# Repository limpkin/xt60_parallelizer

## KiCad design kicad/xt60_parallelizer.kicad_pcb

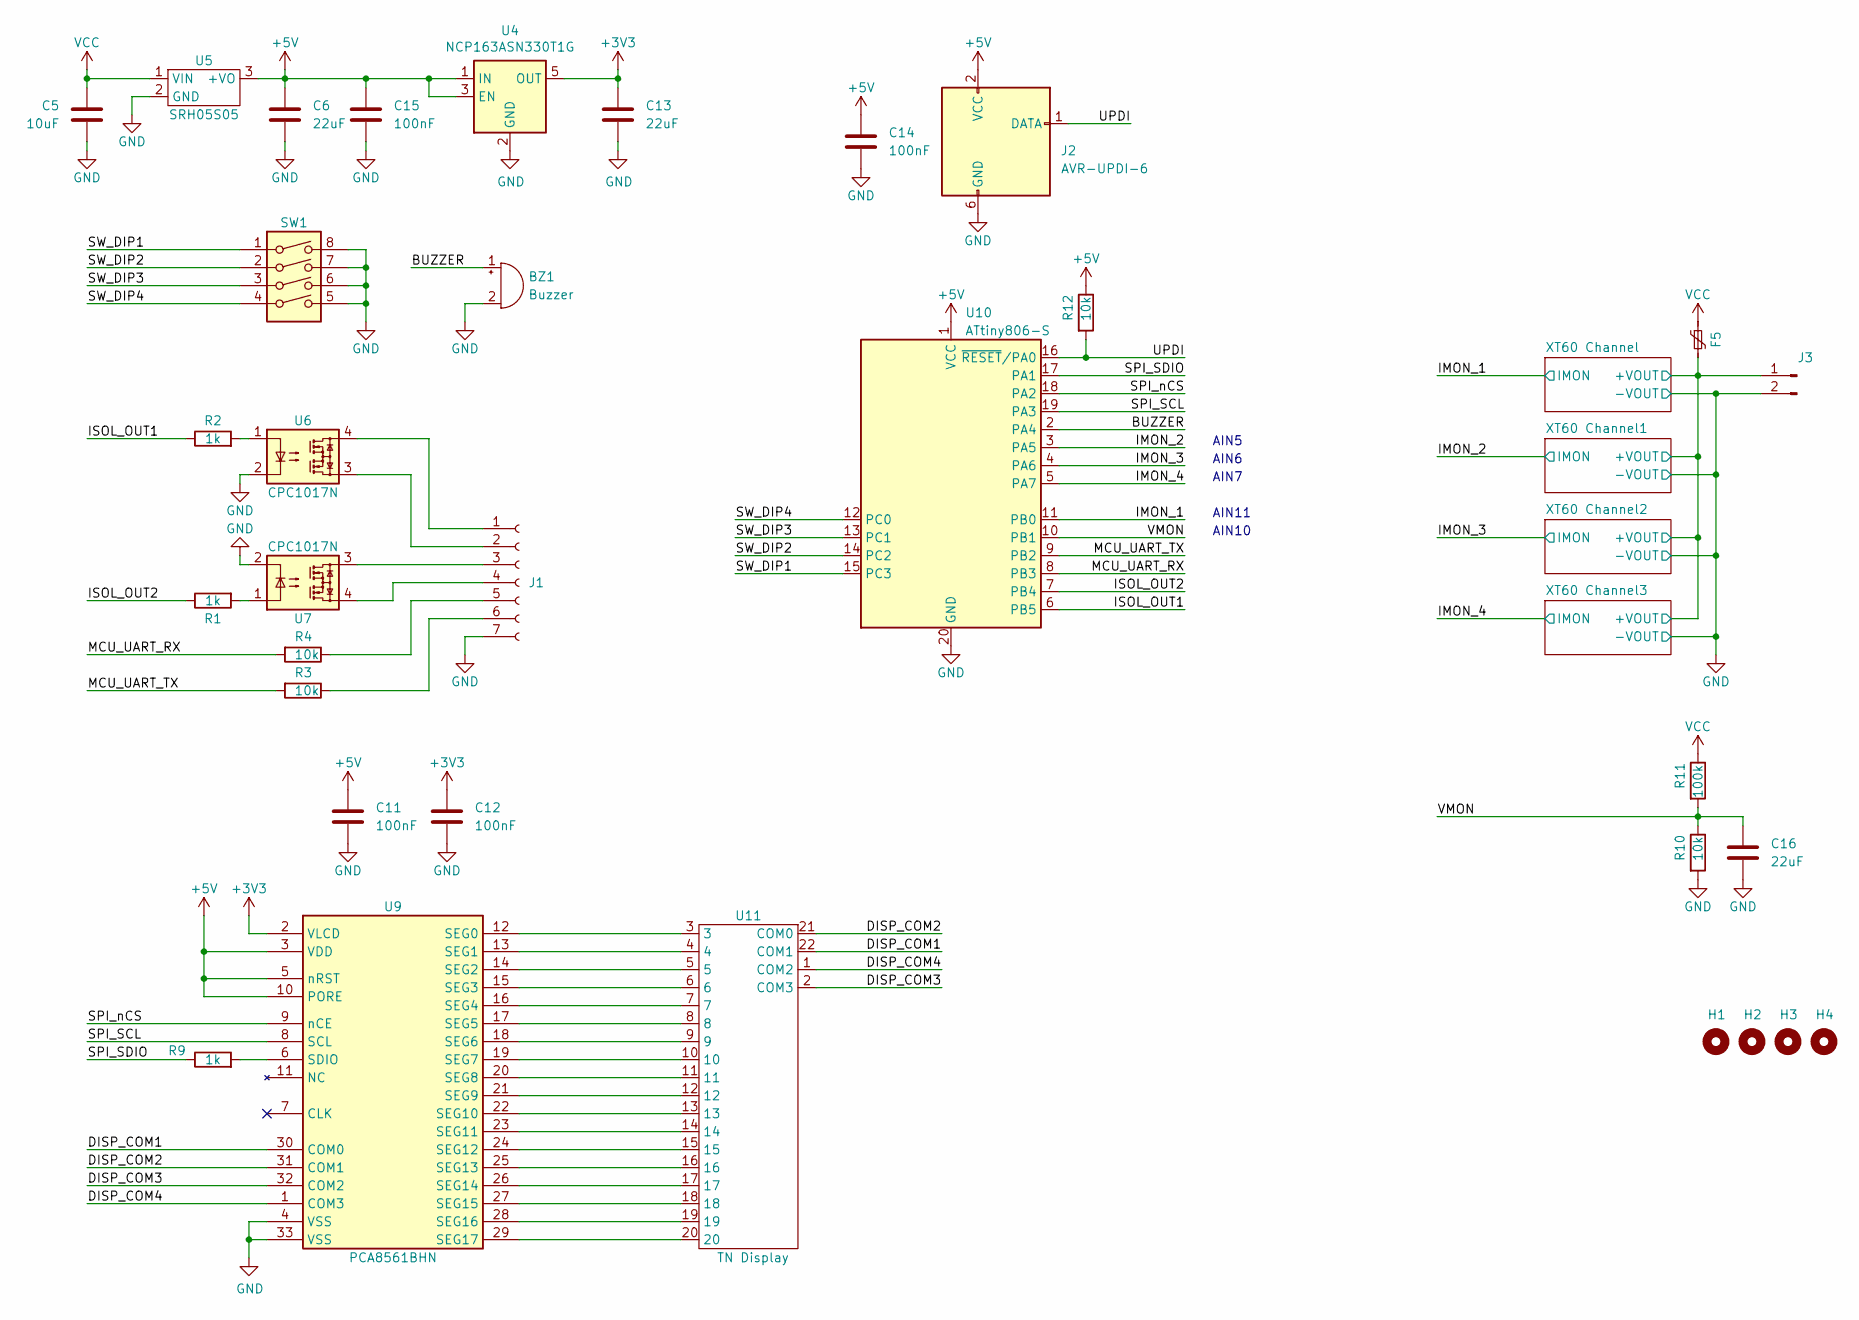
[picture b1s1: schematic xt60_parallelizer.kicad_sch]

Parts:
BZ1: Buzzer; 9042_ACTIVE_BUZZER
C5: 10uF; C_1210_3225Metric
C6, C13, C16: 22uF; C_0805_2012Metric
C11, C12, C14, C15: 100nF; C_0805_2012Metric
F5: Polyfuse_Small; Fuse_1812_4532Metric
H1, H2, H3, H4: MountingHole; MountingHole_3.2mm_M3
J1: Conn_01x07_Socket; PhoenixContact_PTSA_1x07_P3.5mm_Horizontal
J2: AVR-UPDI-6; IDC-Header_2x03_P2.54mm_Vertical
J3: Conn_01x02_Pin; XT60
R1, R2, R9: 1k; R_0805_2012Metric
R3, R4, R10, R12: 10k; R_0805_2012Metric
R11: 100k; R_0805_2012Metric
SW1: SW_DIP_x04; SW_DIP_SPSTx04_Slide_9.78x12.34mm_W7.62mm_P2.54mm
U4: NCP163ASN330T1G; SOT-23-5
U5: SRH05S05; SIP3_11.6x8.5mm_INV
U6, U7: CPC1017N; SOP-4_3.8x4.1mm_P2.54mm
U9: PCA8561BHN; QFN-32-1EP_5x5mm_P0.5mm_EP3.65x3.65mm
U10: ATtiny806-S; SOIC-20W_7.5x12.8mm_P1.27mm
U11: TN Display; 8DIGITS_TN

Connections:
/BUZZER: BZ1.1 (-), U10.2 (PA4)
/DISP_COM1: U9.30 (COM0), U11.22 (COM1)
/DISP_COM2: U9.31 (COM1), U11.21 (COM0)
/DISP_COM3: U9.32 (COM2), U11.2 (COM3)
/DISP_COM4: U9.1 (COM3), U11.1 (COM2)
/IMON_1: U10.11 (PB0); also elsewhere on the board
/IMON_2: U10.3 (PA5); also elsewhere on the board
/IMON_3: U10.4 (PA6); also elsewhere on the board
/IMON_4: U10.5 (PA7); also elsewhere on the board
/ISOL_OUT1: R2.1, U10.6 (PB5)
/ISOL_OUT2: R1.1, U10.7 (PB4)
/MCU_UART_RX: R4.2, U10.8 (PB3)
/MCU_UART_TX: R3.2, U10.9 (PB2)
/SPI_SCL: U9.8 (SCL), U10.19 (PA3)
/SPI_SDIO: R9.1, U10.17 (PA1)
/SPI_nCS: U9.9 (nCE), U10.18 (PA2)
/SW_DIP1: SW1.1, U10.15 (PC3)
/SW_DIP2: SW1.2, U10.14 (PC2)
/SW_DIP3: SW1.3, U10.13 (PC1)
/SW_DIP4: SW1.4, U10.12 (PC0)
/UPDI: J2.1 (DATA), R12.2, U10.16 (~RESET/PA0)
/VMON: C16.1, R10.1, R11.2, U10.10 (PB1)
unnamed: J1.1, U6.4
unnamed: J1.2, U6.3
unnamed: J1.3, U7.3
unnamed: J1.4, U7.4
unnamed: J1.5, R4.1
unnamed: J1.6, R3.1
unnamed: R1.2, U7.1
unnamed: R2.2, U6.1
unnamed: R9.2, U9.6 (SDIO)
unnamed: U9.12 (SEG0), U11.3
unnamed: U9.13 (SEG1), U11.4
unnamed: U9.14 (SEG2), U11.5
unnamed: U9.15 (SEG3), U11.6
unnamed: U9.16 (SEG4), U11.7
unnamed: U9.17 (SEG5), U11.8
unnamed: U9.18 (SEG6), U11.9
unnamed: U9.19 (SEG7), U11.10
unnamed: U9.20 (SEG8), U11.11
unnamed: U9.21 (SEG9), U11.12
unnamed: U9.22 (SEG10), U11.13
unnamed: U9.23 (SEG11), U11.14
unnamed: U9.24 (SEG12), U11.15
unnamed: U9.25 (SEG13), U11.16
unnamed: U9.26 (SEG14), U11.17
unnamed: U9.27 (SEG15), U11.18
unnamed: U9.28 (SEG16), U11.19
unnamed: U9.29 (SEG17), U11.20
VCC: C5.1, F5.1, R11.1, U5.1 (VIN)

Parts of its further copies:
U8: NCP163ASN330T1G; SOT-23-5

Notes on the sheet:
AIN10
AIN6
AIN11
AIN5
AIN7

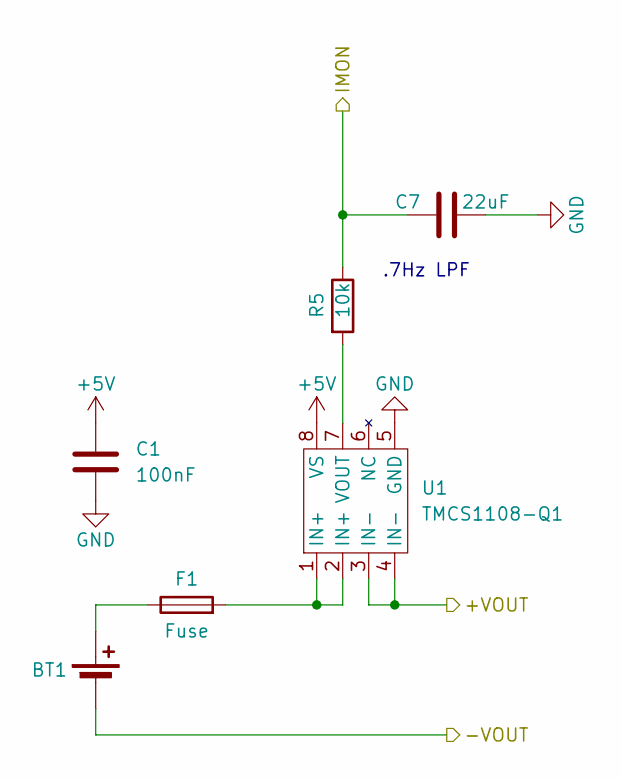
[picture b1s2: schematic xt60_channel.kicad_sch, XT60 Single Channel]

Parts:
BT1: Battery_Cell; XT60
C1: 100nF; C_0805_2012Metric
C7: 22uF; C_0805_2012Metric
F1: Fuse; Fuseholder_Clip-5x20mm_Keystone_3517_Inline_P23.11x6.76mm_D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
R5: 10k; R_0805_2012Metric
U1: TMCS1108-Q1; SOIC-8_3.9x4.9mm_P1.27mm

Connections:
/IMON_1: C7.1, R5.1; also elsewhere on the board
unnamed: BT1.1 (+), F1.1
unnamed: F1.2, U1.1 (IN+), U1.2 (IN+)
unnamed: R5.2, U1.7 (VOUT)

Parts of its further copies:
BT2, BT3, BT4: Battery_Cell; XT60
C2, C3, C4: 100nF; C_0805_2012Metric
C8, C9, C10: 22uF; C_0805_2012Metric
F2, F3, F4: Fuse; Fuseholder_Clip-5x20mm_Keystone_3517_Inline_P23.11x6.76mm_D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
R6, R7, R8: 10k; R_0805_2012Metric
U2, U3: TMCS1108-Q1; SOIC-8_3.9x4.9mm_P1.27mm

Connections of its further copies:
/IMON_2: C8.1, R6.1; also elsewhere on the board
/IMON_3: C9.1, R7.1; also elsewhere on the board
/IMON_4: C10.1, R8.1; also elsewhere on the board
unnamed: BT2.1 (+), F2.1
unnamed: BT3.1 (+), F3.1
unnamed: BT4.1 (+), F4.1
unnamed: F2.2, U2.1 (IN+), U2.2 (IN+)
unnamed: F3.2, U3.1 (IN+), U3.2 (IN+)
unnamed: R6.2, U2.7 (VOUT)
unnamed: R7.2, U3.7 (VOUT)
unnamed 40: R8.2; also elsewhere on the board

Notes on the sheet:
.7Hz LPF

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
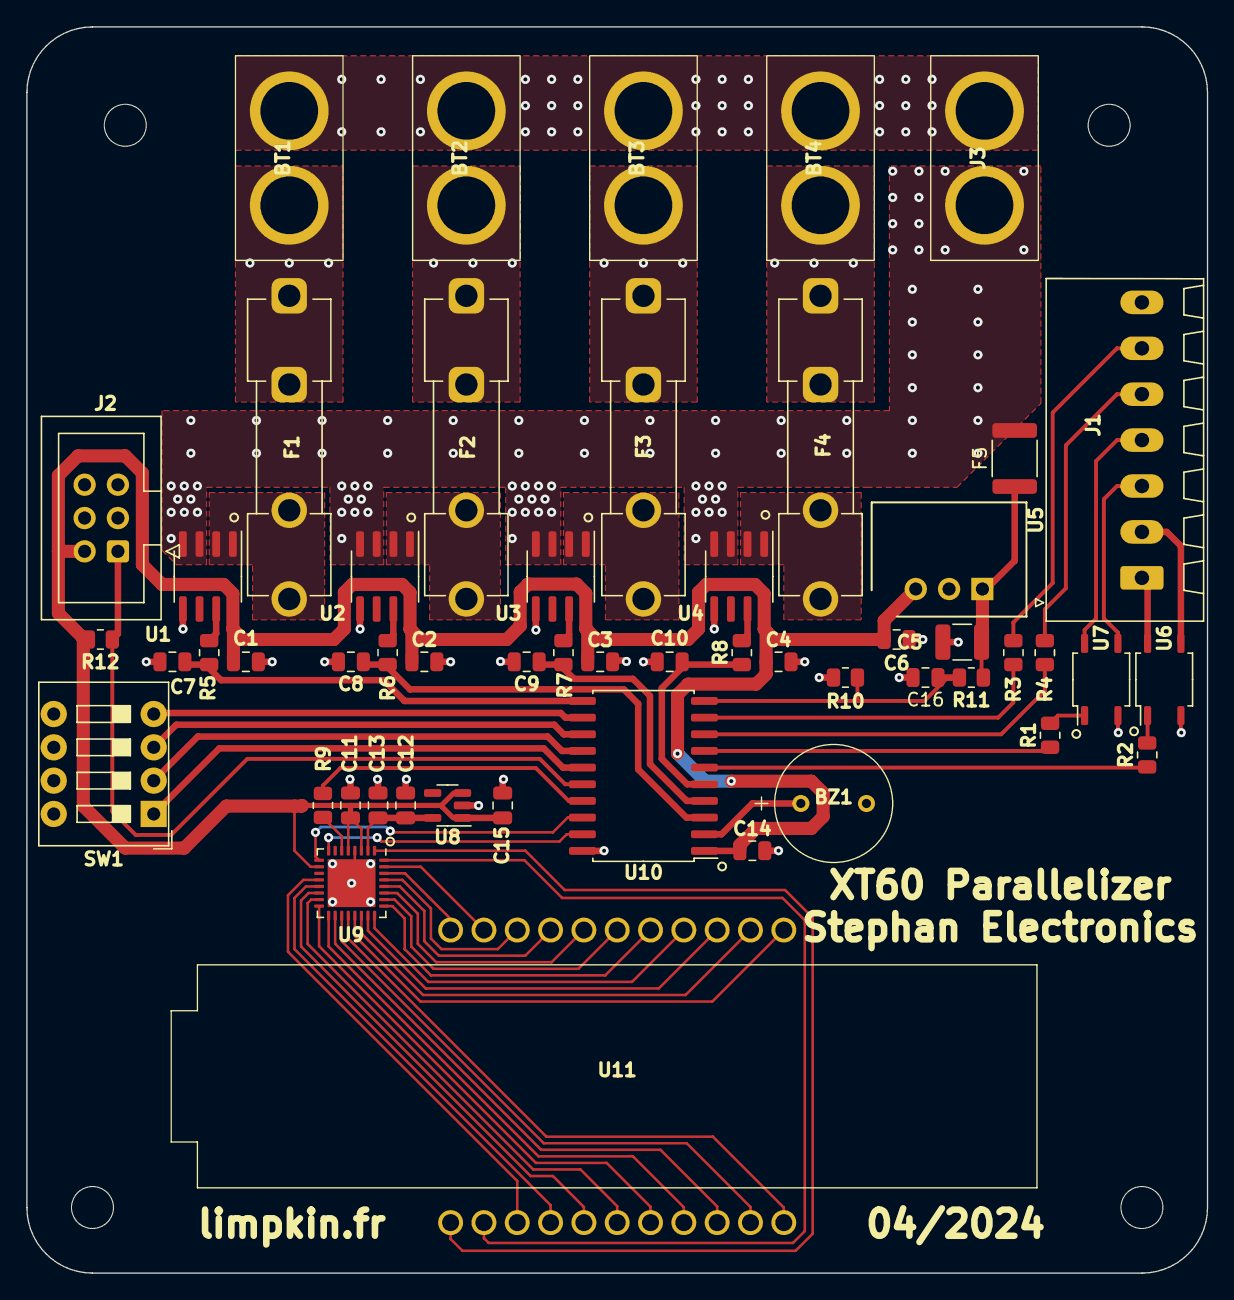
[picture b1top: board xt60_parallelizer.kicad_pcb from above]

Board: 2 copper layers, 90.0 x 95.0 mm, 57 parts (0 on the bottom side), 66 nets.

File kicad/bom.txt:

Reference	Value	Qty	Manufacturer	Manufacturer Part Number
C1,C2,C3,C4,C11,C12,C14,C15	100nF	8	Samsung Electro-Mechanics	CL21B104KBCNNNC
C5	10uF	1	Murata Electronics	GRM32EC72A106KE05L
C6,C7,C8,C9,C10,C13,C16	22uF	7	Samsung Electro-Mechanics	CL21A226MOCLRNC
F5	Polyfuse_Small	1	Littelfuse Inc.	MINISMDC014F-2
J1	Conn_01x07_Socket	1	Phoenix Contact	1985014
J2	AVR-UPDI-6	1	TE Connectivity AMP Connectors	1761681-1
R1,R2,R9	1k	3	YAGEO	RC0805FR-071KL
R3,R4,R5,R6,R7,R8,R10,R12	10k	8	YAGEO	RC0805FR-0710KL
R11	100k	1	YAGEO	RC0805FR-07100KL
U1,U2,U3,U4	TMCS1108-Q1	4	Texas Instruments	TMCS1108A3BQDRQ1
U5	SRH05S05	1	XP Power	SRH05S05
U6,U7	CPC1017N	2	IXYS Integrated Circuits Division	CPC1017NTR
U8	 NCP163ASN330T1G	1	onsemi	NCP163ASN330T1G
U9	PCA8561BHN	1	NXP USA Inc.	PCA8561BHN/AY
U10	ATtiny806-S	1	Microchip Technology	ATTINY806-SN
